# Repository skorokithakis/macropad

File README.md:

# Stavropad

A 4x4 macro pad running ZMK firmware on a Nice!Nano v2.

## Features

- 15 normal layers with 15 usable keys each
- Layer switching via dedicated layer-switching key
- All hotkey layers send RCtrl+Shift+Cmd + a character (for use as global hotkeys)
- Idle deep sleep enabled; wakes on any key press after inactivity
- 15 Bluetooth profiles via dedicated Bluetooth control screen

## Layer access

Hold the layer-switching key (bottom-right, key 15) to activate the layer switcher. While holding it:

**Normal layers (tap):**
- Tap keys 0-11 to switch to normal layers 0-11.
- Tap keys 12-14 to switch to normal layers 12-14.

**Special layers (hold for 1 second, ordered by increasing danger):**
- Key 0: Type battery voltage (for example: "Battery: 3.98V").
- Key 1: Open Bluetooth control.
- Key 2: Enter bootloader mode.

## Layers

See [KEYMAPS.md](KEYMAPS.md) for visual layer references.

```
Key positions:
 0   1   2   3
 4   5   6   7
 8   9  10  11
12  13  14  15
```

**Normal layers**

- **Layer 0**: Hotkeys (numbers and symbols)
- **Layer 1**: Hotkeys (letters A-P)
- **Layer 2**: Hotkeys (letters Q-Z and punctuation)
- **Layer 3**: Hotkeys (function keys and modifiers)
- **Layer 4**: Text macros
- **Layer 5**: Media controls
- **Layer 6**: Mouse control
- **Layer 7**: Gaming
- **Layer 8**: Numpad
- **Layer 9**: Cluster
- **Layer 10**: OnShape Sketch Tools
- **Layers 11-14**: Placeholder layers

**Special layers**

- **Bluetooth control**: Select Bluetooth profiles 0-14 and clear bonds.
- **Battery voltage**: Types a voltage readout.
- **Bootloader**: Enters bootloader mode.

**OnShape sub layers (accessed from Layer 10)**

- **Layer 18**: OnShape Constraints (hold key 10). Shortcuts: D, H, V, I, T, E, B, Shift + L, Shift + O, Shift + M, Shift + Q, Shift + J, Shift + K, Shift + U, Shift + G.
- **Layer 19**: OnShape Features (hold Escape). Shortcuts: Shift + E (Extrude), Shift + W (Revolve), Shift + F (Fillet). Remaining keys are empty.
- **Layer 20**: OnShape Numbers (hold key 11). Numpad layout (7-8-9, 4-5-6, 1-2-3, 0) with *, mm macro, +, decimal point, and backspace.
## Customize

Edit `config/stavropad.keymap`.

## Building

Run the build script:

```bash
./build.sh        # PCB version (default)
./build.sh -v 1   # Hand-wired version
./build.sh -v 2   # PCB version
```

This uses Docker to build the firmware. Output is `build/zephyr/zmk.uf2`.
The custom shield and keymap live under `config/boards/shields/stavropad`.

Pin mappings for each version are in `pins_v1.overlay` and `pins_v2.overlay`.

## Flashing

1. Put the board in bootloader mode (hold the layer-switching key + hold key 2 for 1 second).
2. Copy `build/zephyr/zmk.uf2` to the USB mass storage device that appears.

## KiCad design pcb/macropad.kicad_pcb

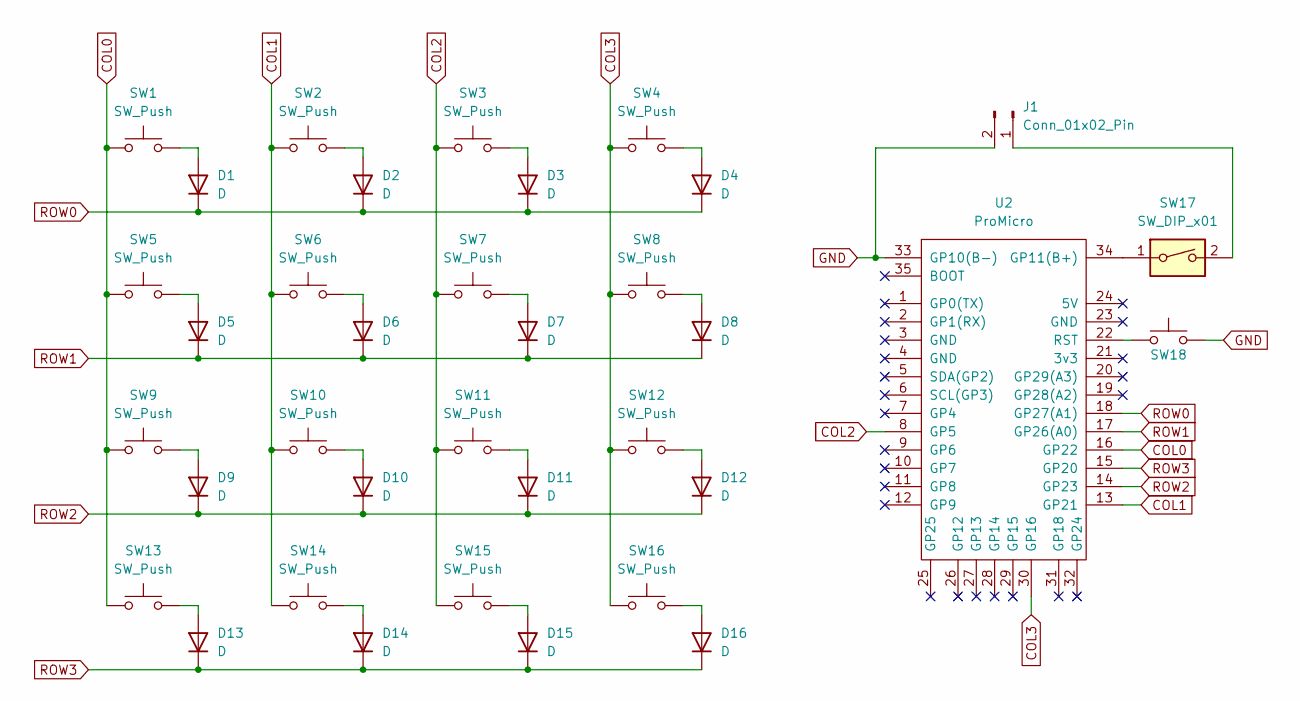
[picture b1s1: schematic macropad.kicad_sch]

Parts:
D1, D2, D3, D4, D5, D6, D7, D8, D9, D10, D11, D12, D13, D14, D15, D16: D; D_SOD-323; LCSC C2128
J1: Conn_01x02_Pin; PinHeader_1x02_P2.54mm_Vertical
SW1, SW2, SW3, SW4, SW5, SW6, SW7, SW8, SW9, SW10, SW11, SW12, SW13, SW14, SW15, SW16: SW_Push; SW_MX_Kailh_Choc_V1V2_HotSwap_Hybrid
SW17: SW_DIP_x01; SW_SPDT_Shouhan_MSK12C02
SW18: SW_Push; SW_SPST_TS-1088-xR020; LCSC C720477
U2: ProMicro; TheOneProMacro

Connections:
COL0: SW1.1, SW5.1, SW9.1, SW13.1, U2.16 (GP22)
COL1: SW2.1, SW6.1, SW10.1, SW14.1, U2.13 (GP21)
COL2: SW3.1, SW7.1, SW11.1, SW15.1, U2.8 (GP5)
COL3: SW4.1, SW8.1, SW12.1, SW16.1, U2.30 (GP16)
GND: J1.2, SW18.2, U2.33 (GP10(B-))
unnamed: D1.2 (A), SW1.2
unnamed: D2.2 (A), SW2.2
unnamed: D3.2 (A), SW3.2
unnamed: D4.2 (A), SW4.2
unnamed: D5.2 (A), SW5.2
unnamed: D6.2 (A), SW6.2
unnamed: D7.2 (A), SW7.2
unnamed: D8.2 (A), SW8.2
unnamed: D9.2 (A), SW9.2
unnamed: D10.2 (A), SW10.2
unnamed: D11.2 (A), SW11.2
unnamed: D12.2 (A), SW12.2
unnamed: D13.2 (A), SW13.2
unnamed: D14.2 (A), SW14.2
unnamed: D15.2 (A), SW15.2
unnamed: D16.2 (A), SW16.2
unnamed: J1.1, SW17.2
unnamed: SW17.1, U2.34 (GP11(B+))
unnamed: SW18.1, U2.22 (RST)
ROW0: D1.1 (K), D2.1 (K), D3.1 (K), D4.1 (K), U2.18 (GP27(A1))
ROW1: D5.1 (K), D6.1 (K), D7.1 (K), D8.1 (K), U2.17 (GP26(A0))
ROW2: D9.1 (K), D10.1 (K), D11.1 (K), D12.1 (K), U2.14 (GP23)
ROW3: D13.1 (K), D14.1 (K), D15.1 (K), D16.1 (K), U2.15 (GP20)

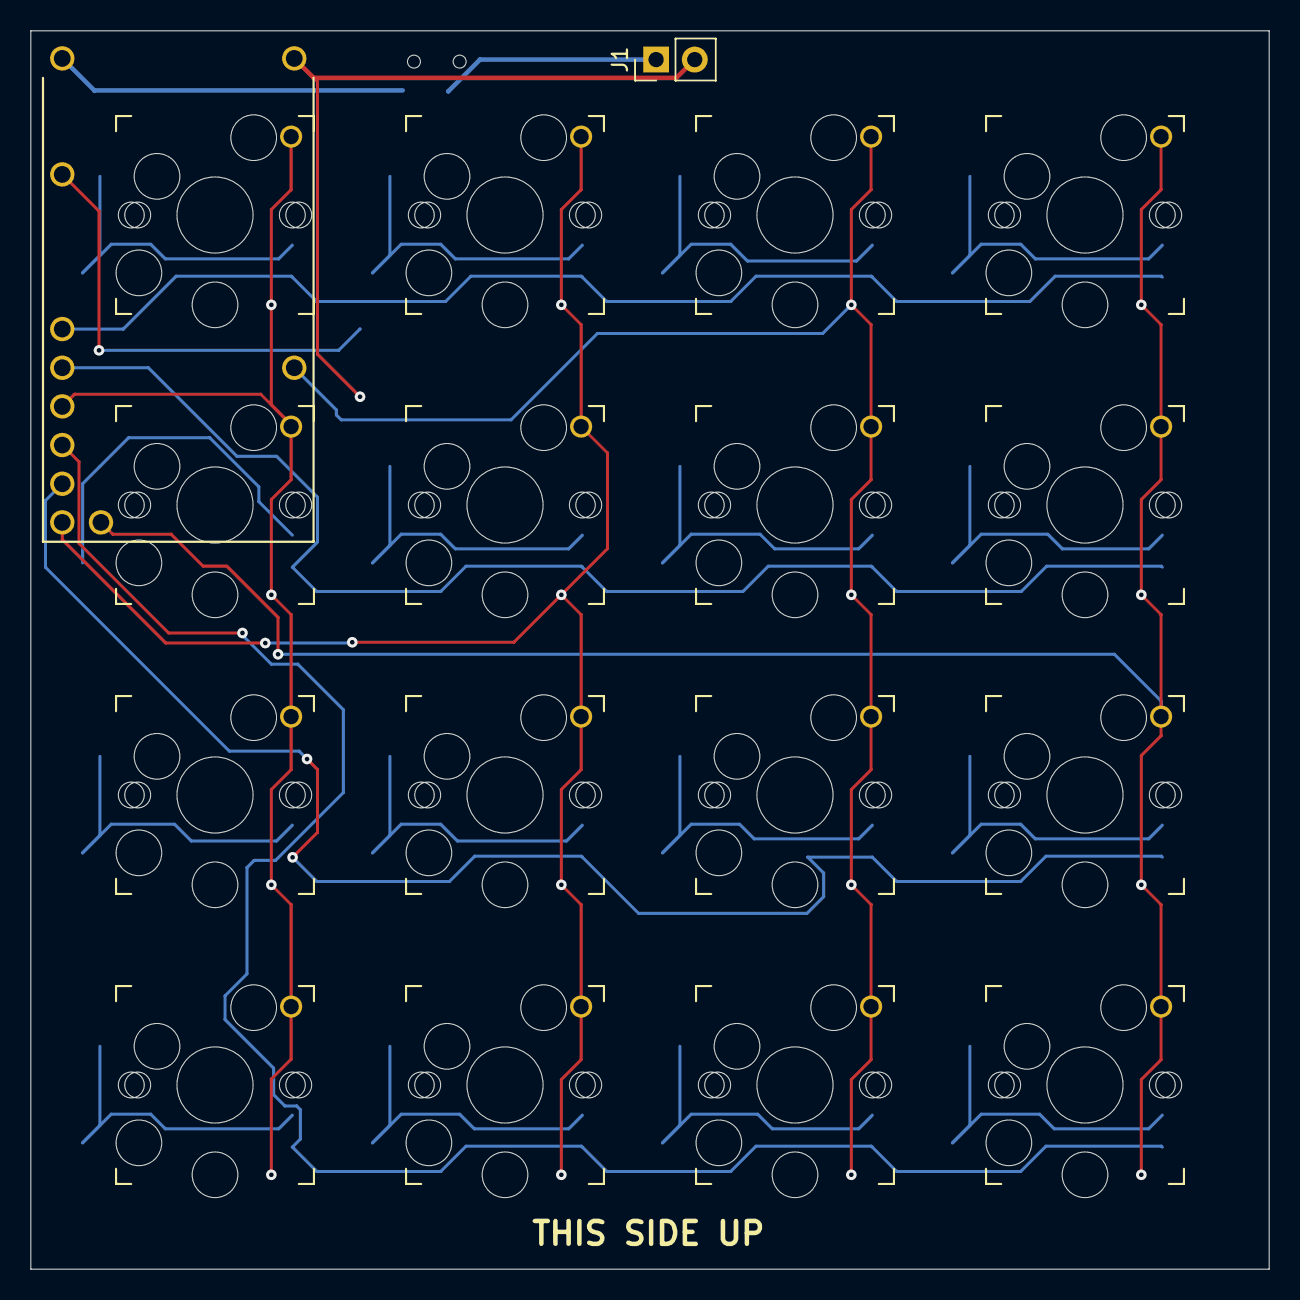
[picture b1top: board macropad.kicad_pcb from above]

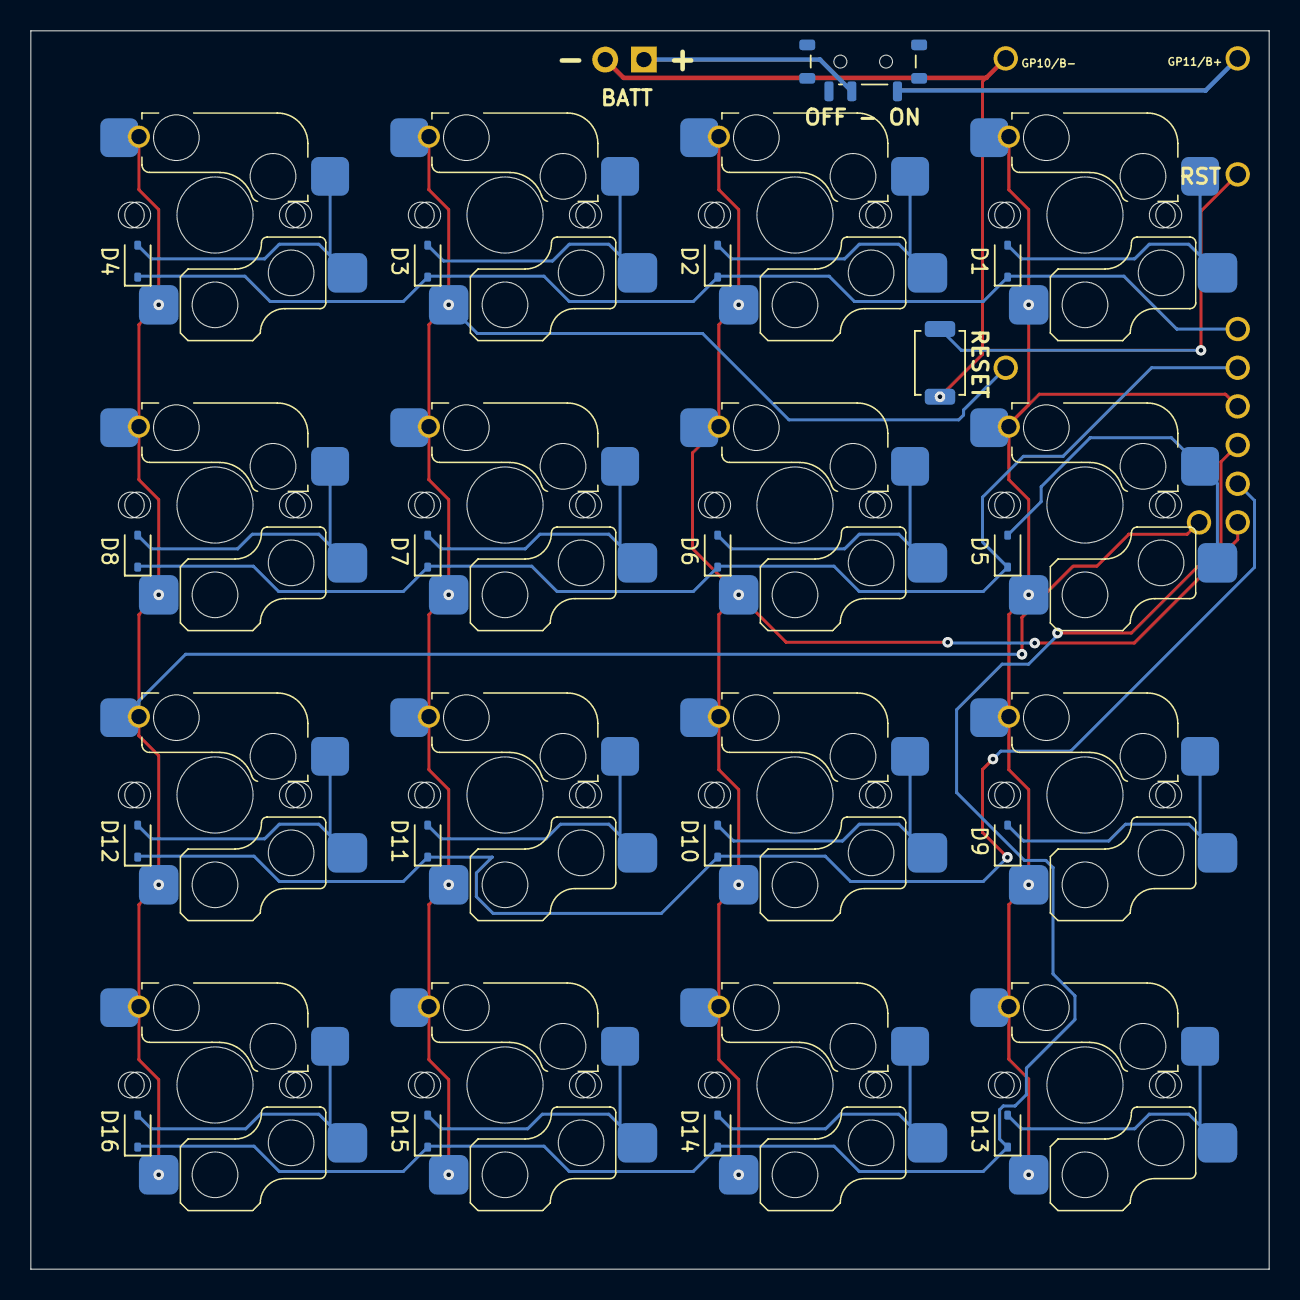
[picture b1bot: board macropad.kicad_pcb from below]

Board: 2 copper layers, 81.3 x 81.3 mm, 36 parts (18 on the bottom side), 28 nets.

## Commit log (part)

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2025-12-30 Updates?
2025-12-30 Add layers and shortcuts
2025-12-30 Fix build script
2025-12-30 Attempt to find safer hotkeys
2025-12-30 Clear Bluetooth pairings with a key combo
2025-12-30 Add README
2025-12-31 Use right control key instead of left control for shortcuts
    Switches all keyboard shortcuts from LC (left control) to RC (right control)
    to avoid conflicts with caps lock when users have swapped caps and control keys.
2025-12-31 15 layers
2025-12-31 Add gaming layer
2025-12-31 Add battery voltage display key combination
    - Add battery_voltage_macro that types "Battery: 3.98V"
    - Configure combo for middle two layer buttons (1 and 2) to trigger the macro
    - Update README to document the new feature
    - Note: Displays static voltage value; real-time voltage would require custom firmware
2025-12-31 Implement real-time battery voltage display with custom ZMK behavior
    Replace static battery voltage macro with a custom ZMK behavior that reads
    actual battery voltage on-demand. This implementation:
    - Adds batt_type custom behavior module that reads battery sensor
    - Reads voltage via standard ZMK battery API (/chosen zmk,battery)
    - Converts voltage to text and types it as HID keystrokes (e.g., "3.98V")
    - Triggers on middle two layer buttons (positions 1 and 2) combo
2025-12-31 Add hold-tap behavior for battery voltage combo
    Change battery voltage combo to use hold-tap behavior:
    - Long-press buttons 1+2: Types battery voltage (e.g., "3.98V")
    - Short-press buttons 1+2: Activates layer 7 (preserves original functionality)
    This follows the same pattern as bootloader and BT clear combos, providing
    dual functionality on a single key combination. The 1-second hold time
    matches other hold-tap behaviors in the keymap.
2025-12-31 Fix the battery voltage
2025-12-31 Change what's typed
2025-12-31 Fix small overflow
2025-12-31 Fix GitHub action
2025-12-31 Fix ZMK module path and add required module.yml
    This fixes the GitHub Actions build failure by:
    1. Adding the required zephyr/module.yml file to the batt_type module
    - Zephyr requires this file to recognize a directory as a valid module
    2. Updating the ZMK_EXTRA_MODULES path in build.yaml to use ${GITHUB_WORKSPACE}
    - This ensures the path is correctly resolved in the GitHub Actions environment
    The error "is not a valid zephyr module" was caused by the missing module.yml file.
2025-12-31 Fix ZMK_EXTRA_MODULES to include both repository root and batt_type module
    The previous version was only passing the batt_type module path, which caused
    the build to fail with "No shield named 'macropad' found". This is because the
    repository root contains zephyr/module.yml which defines board_root, needed to
    locate the macropad shield in boards/shields/macropad/.
    CMake requires multiple module paths to be passed as a semicolon-separated list
    in a single -D flag, not as separate -D flags (which would override each other).
2025-12-31 Update build.sh to include repository root in ZMK_EXTRA_MODULES
    Makes the local build script consistent with the GitHub Actions build.yaml
    by including both the repository root and the batt_type module.
    This ensures the build can find:
    - The macropad shield definition (from zephyr/module.yml board_root setting)
    - The custom batt_type module
    While the local build may have worked before (since ZMK_CONFIG points to
2025-12-31 Fix build
2025-12-31 Fix build (#4)
    * Fix build
    * Fix build
2026-01-01 Add deep sleep
2026-01-01 Add battery typing delays
2026-01-01 Add Bluetooth profile layer
2026-01-02 Add Gio Kay layer, because what else are you gonna do
2026-01-02 Add initial PCB
2026-01-02 More laying out
2026-01-03 Improvements
2026-01-04 Add PCB (#5)
2026-01-04 Add media control layer (layer 5, buttons 0+2)
    Layer includes brightness, volume, playback controls, shuffle/repeat, and search.
2026-01-07 Make more compatible
2026-01-08 Replace TAB with Left Shift in macropad keymap
2026-01-21 Change things
2026-01-21 Fix +/- silkscreen
2026-01-21 Change pin assignments to the PCB ones
2026-01-21 Change macropad name
2026-01-21 Add selectable v1/v2 pin overlays and update build/docs
2026-01-26 Allow pointing and higher TX
2026-01-26 Add pointing (mouse/scroll) layers, update keymap/README, ignore misc
2026-01-26 Introduce layer-16 selection, key12 hold-tap behaviors and macros
2026-01-26 Revise layer switching and remap layers/special functions
2026-01-26 Document layer access and update Bluetooth profiles to 15
2026-01-30 Update Layer 4 macros: replace aristotelis with doulevo san pisinos
2026-01-30 Rename phrase_nootropia to phrase_notropia and correct binding
2026-01-31 Increase buffer size
2026-01-31 Add more instructions
2026-01-31 Move macropad.keymap to config/ and replace with symlink
2026-01-31 Rename to Stavropad
2026-01-31 Add Stavropad config file
2026-01-31 Add config rendering
2026-01-31 Add OnShape sketch layers, macros, layouts; update docs
2026-01-31 Add pre-commit KLE render hook, KEYMAPS.md and layouts
2026-01-31 Enforce 5-char key labels, abbreviate layouts, crop KLE renders
2026-01-31 Update OnShape Sketch layer layout and keymap; simplify docs
2026-01-31 Add layer images
2026-02-01 Remap OnShape constraint keys, clear features, update README/images
2026-02-01 Change silkscreen text from ON/OFF to OFF - ON
2026-02-04 Add Layer 20 OnShape Numbers and support in keymap and render script
2026-02-04 Regenerate layout images and resize KLE renders to half
2026-02-04 Add Delete key to Onshape sketch layer layout and keymap
2026-02-08 Layer 10 key 11: tap sends Ctrl+Z (undo), hold activates Numbers
2026-02-13 Group related layout layers by filename prefix in KEYMAPS.md
2026-02-14 Add repository overview and post-change checklist to AGENTS.md
2026-02-14 Move layer-switching key from key 12 (bottom-left) to key 15 (bottom-right)
    Shift bottom-row bindings (keys 13-15 → 12-14) on all 21 layers.
    Resolve hold-down conflicts on the new layer-switching position:
    - Layer 6 (Mouse): rotate all columns left so right-click isn't on key 15
    - Layer 7 (Gaming): swap Space and Enter so Space isn't on key 15
    - Layer 10 (OnShape): move hold-for-constraints from key 15 to key 10
    - Layer 20 (OnShape Numbers): move Backspace from key 15 to key 11
2026-02-14 Change keys back
2026-02-14 Some fixes
2026-02-14 Re-render keymaps
2026-02-18 Remember active layer when going to sleep
2026-02-26 Fix OnShape numbers layout
